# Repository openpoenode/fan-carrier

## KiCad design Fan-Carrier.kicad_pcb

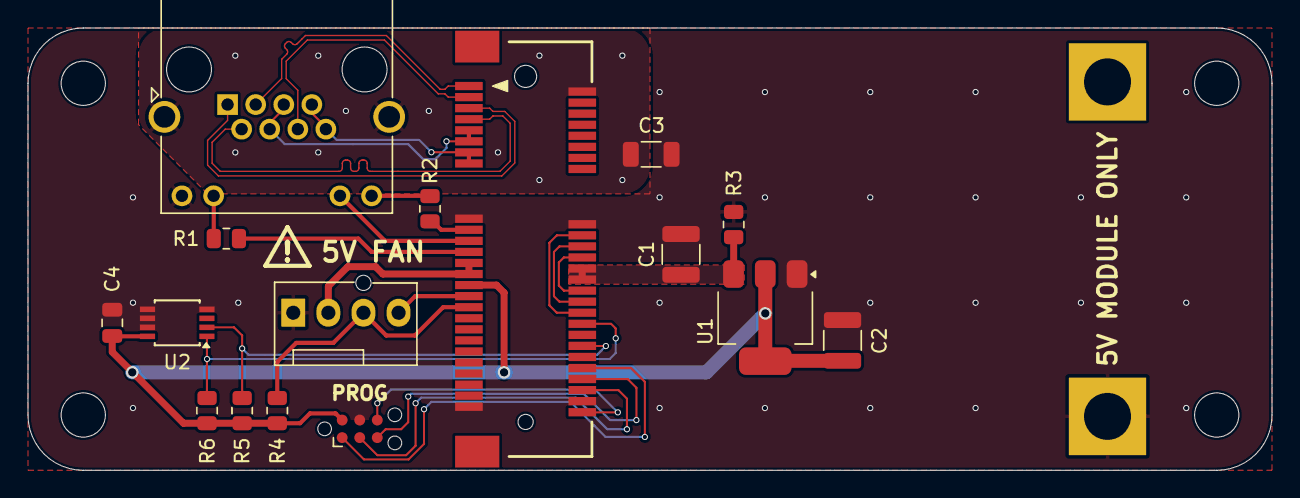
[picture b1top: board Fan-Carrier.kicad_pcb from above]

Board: 2 copper layers, 90.0 x 32.0 mm, 21 parts (0 on the bottom side), 26 nets.

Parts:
C1: 10uF; C_1210_3225Metric
C2: 22uF; C_1210_3225Metric
C3: 2200pF 2kV; C_1206_3216Metric
C4: 100nF; C_0805_2012Metric
H1, H2, H3, H4: MountingHole; MountingHole_3.2mm_M3
J1: TC2030; Tag-Connect_TC2030-IDC-NL_2x03_P1.27mm_Vertical
J2: RJHSE-5381; RJ45_Amphenol_RJHSE538X
J3: 119A-80A00-R02
J4: 119A-NUT-80-R02
M1: Fan_4pin; FanPinHeader_1x04_P2.54mm_Vertical
R1, R2: 270R; R_0805_2012Metric
R3: 100R 0.5W; R_0805_2012Metric
R4, R5, R6: 10K; R_0805_2012Metric
U1: AZ1117-3.3; SOT-223-3_TabPin2
U2: LM75; TSSOP-8_3x3mm_P0.65mm

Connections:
+3.3V: C2.1, C4.2, J1.2, J3.29 (Vcc), R4.1, R5.1, R6.1, U1.2 (VO), U2.8 (+Vs)
+5V: C1.1, J3.25 (Vout), J3.26 (Vout), J3.27 (Vout), J3.28 (Vout), M1.2 (+), R3.1, U1.3 (VI)
/3V3A: J3.19 (3V3A), R2.1
/ETH_LED1: J3.23 (LED1/Act), R1.1
/ETH_LED2: J2.11, J3.21 (LED2/Speed)
/GPIO0: J1.6, J3.52 (GPIO0)
/MDC: J3.22 (MDC), J3.32 (GPIO18)
/MDIO: J3.24 (MDIO), J3.30 (GPIO5)
/P1N: J2.2, J3.7 (2)
/P1P: J2.1, J3.5 (1)
/P2N: J2.6, J3.3 (6)
/P2P: J2.3, J3.1 (3)
/P3: J2.4, J2.5, J3.9 (4/5), J3.11 (4/5)
/P4: J2.7, J2.8, J3.13 (7/8), J3.15 (7/8)
/PHY_EN: J3.20 (PHY_EN), J3.34 (GPIO4)
/RXD: J1.5, J3.46 (UART_RXD)
/SCL: J3.40 (GPIO15), R5.2, U2.2 (SCL)
/SDA: J3.36 (GPIO13), R6.2, U2.1 (SDA)
/SPEED: J3.31 (GPIO23), M1.4 (PWM)
/TACH: J3.33 (GPIO36), M1.3 (Tacho), R4.2
/TXD: J1.3, J3.48 (UART_TXD)
/~RST: J1.1, J3.44 (~MCU_RST)
Earth: C3.2, J2.SH, J3.2 (BST)
GND: C1.2, C2.2, C3.1, C4.1, J1.4, J2.9, J3.17 (GND), J3.18 (GND), J3.50 (GND), J3.51 (GND), J4.2, M1.1 (-), R3.2, U1.1 (GND), U2.4 (GND), U2.5 (A2), U2.6 (A1), U2.7 (A0)
unnamed: J2.10, R1.2
unnamed: J2.12, R2.2

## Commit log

2026-03-19 finished PCB artwork
2026-03-19 added LICENSE
2026-03-19 added IDAnything
2026-03-29 increased thermal relief updated holddown nut solder paste pattern
2026-03-29 prettification
